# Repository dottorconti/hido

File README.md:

# HIDO - Arcade Multi-Mode Controller

Open source arcade controller with STM32F102RB microcontroller.

## 🎮 Features

- **Triple Mode Support**: NKRO Keyboard, Dual Joystick, or JVS/RS485
- **Ultra-Low Latency**: 1ms USB polling (1000Hz)
- **Plug & Play**: Standard USB HID device, no drivers needed
- **Hardware Debouncing**: 5ms configurable debounce time
- **Dual Player Support**: 2 independent joystick interfaces (34 inputs total)

## 📚 Documentation

### Quick Links
- **[📋 PINOUT.md](doc/PINOUT.md)** - Complete pin mapping and silkscreen reference
- **[🔧 Firmware Documentation](doc/README.md)** - Detailed firmware guide
- **[🔨 Build & Compilation](doc/COMPILATION.md)** - How to build the firmware (scripts and legacy method)
- **[⚡ Quick Start Guide](doc/QUICK_START.md)** - Get started quickly
- **[🔄 Mode Comparison](doc/MODE_COMPARISON.md)** - Keyboard vs Joystick vs JVS
- **[⚙️ Hardware Configuration](doc/HARDWARE_CONFIG.md)** - Hardware setup
- **[🕹️ JVS Protocol](doc/JVS_PROTOCOL.md)** - JVS/RS485 arcade protocol
- **[📝 Changelog](doc/CHANGELOG.md)** - Version history
- **[👥 Credits](doc/CREDITS.md)** - Contributors and licenses

## 🚀 Quick Start

1. **Connect your arcade controls** - See [PINOUT.md](doc/PINOUT.md) for connector pinout
2. **Select operating mode** - Edit `firmware/Core/Inc/usbd_hid_custom.h`
3. **Compile and flash** - See [Quick Start Guide](doc/QUICK_START.md)
4. **Plug and play** - Device recognized as USB HID

## 🛠️ Hardware

- **MCU**: STM32F102RB (Cortex-M3, 128KB Flash)
- **USB**: Full-Speed USB 2.0 (12 Mbps)
- **Connectors**: J6 (Player 1), J7 (Player 2) - 18 pins each
- **Inputs**: 34 digital inputs (17 per player) with pull-up resistors
- **LEDs**: Debug indicators (LED1=P1, LED2=P2)

## 📋 Pin Mapping Reference

Each connector has **silkscreen labels** (0-9, A-F, 10) for easy identification:

| Silkscreen | Pin | Player 1 Key | Player 2 Key |
|------------|-----|--------------|--------------|
| COM | 1 | GND | GND |
| 0 | 2 | Z | A |
| 1 | 3 | X | S |
| 2 | 4 | C | D |
| ... | ... | ... | ... |
| 10 | 18 | ↑ | F1 |

**See [PINOUT.md](doc/PINOUT.md) for complete mapping.**

## 🔌 Operating Modes

### Keyboard Mode (6KRO)
Standard USB keyboard with 6-key rollover for arcade gaming.

### Joystick Mode
Dual USB joystick with 13 logical buttons + 2 axes each (per player).

Note (recent fixes):
- Firmware expects 13 logical buttons per player (bits 0..12).
- Natural mapping restored: Report ID 1 -> Player 1, Report ID 2 -> Player 2.
- Removed blocking `HAL_Delay(1)` between HID reports to avoid USB freezes.
- Firmware now only sends HID reports when the report contents change (reduces USB traffic).
- If Player 2 feels slow, try reducing `DEBOUNCE_TIME_MS` in `Core/Inc/arcade_joystick.h` to 2-3 ms.

### JVS Mode
RS485 arcade I/O board protocol for JAMMA/JVS cabinets.

**See [Mode Comparison](doc/MODE_COMPARISON.md) for details.**

## 📦 Repository Structure

```
hido/
├── README.md
├── doc/                   # Documentation
│   ├── CHANGELOG.md
│   ├── CORREZIONI_RS485_5V.md
│   ├── CREDITS.md
│   ├── DFU_UPDATE.md
│   ├── HARDWARE_CONFIG.md
│   ├── JVS_PROTOCOL.md
│   ├── MODE_COMPARISON.md
│   ├── PINOUT.md
│   ├── QUICK_START.md
│   └── README.md
├── fabrication/           # Gerber / manufacturing files
├── firmware/              # STM32 firmware source and tools
│   ├── build.ps1
│   ├── check_dfu_util.bat
│   ├── compile_direct.ps1
│   ├── config_tool.py
│   ├── dfu_update.bat
│   ├── dfu_update.py
│   ├── download_dfu_util.bat
│   ├── flash.ps1
│   ├── hido.ioc
│   ├── LICENSE
│   ├── Makefile
│   ├── STM32F102RBTX_FLASH.ld
│   ├── Core/
│   │   ├── Inc/
│   │   ├── Src/
│   │   └── Startup/
│   ├── Drivers/
│   │   └── STM32F1xx_HAL_Driver/
│   ├── Middlewares/
│   │   └── ST/STM32_USB_Device_Library/
│   ├── tools/
│   └── USB_DEVICE/
├── hardware/              # KiCad design & PCB files
│   ├── Jopen.kicad_pcb
│   ├── Jopen.kicad_sch
│   ├── mcu.kicad_sch
│   ├── rs485.kicad_sch
│   └── Jopen-backups/     # local backups (should be ignored)
└── tools/                 # helper scripts and utilities
```

## 📄 License

See [CREDITS.md](doc/CREDITS.md) for license information.

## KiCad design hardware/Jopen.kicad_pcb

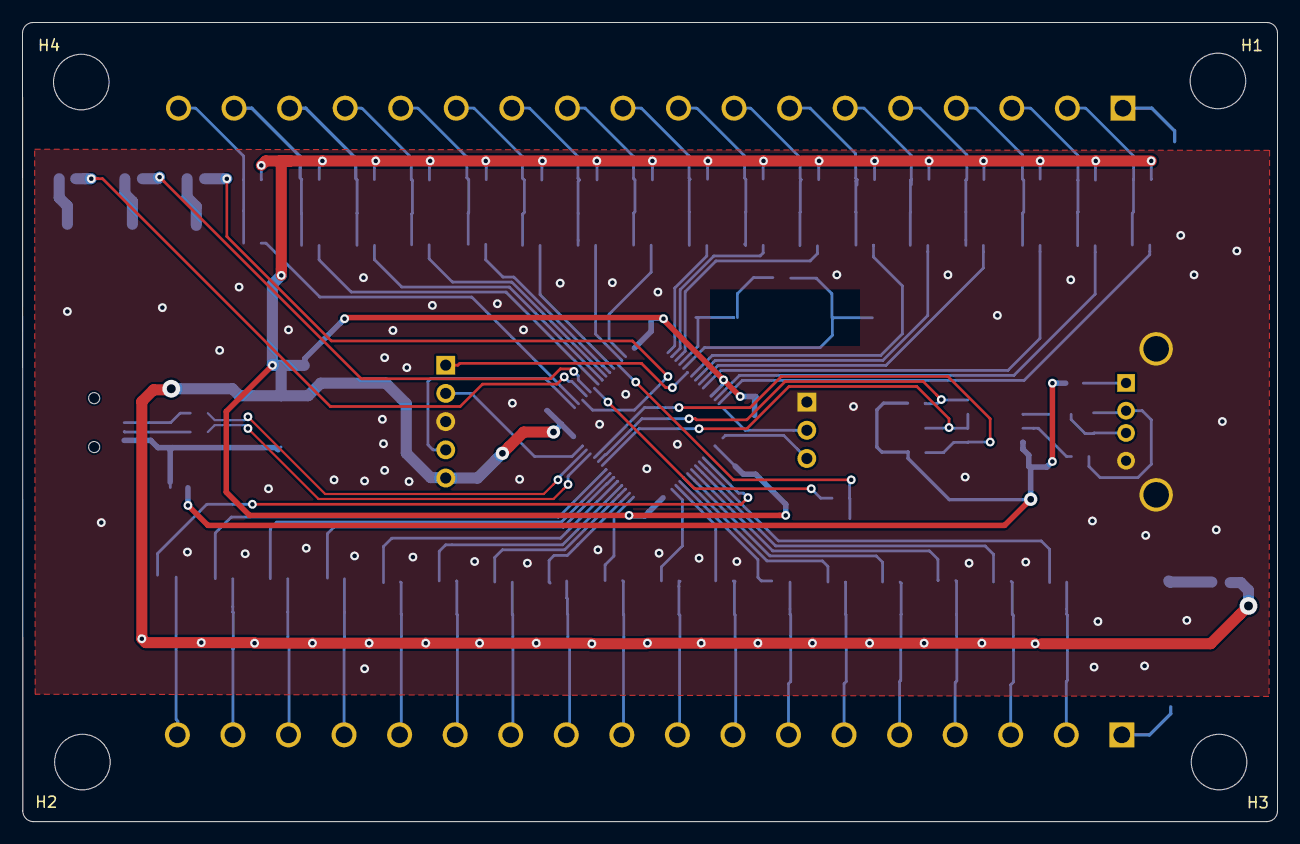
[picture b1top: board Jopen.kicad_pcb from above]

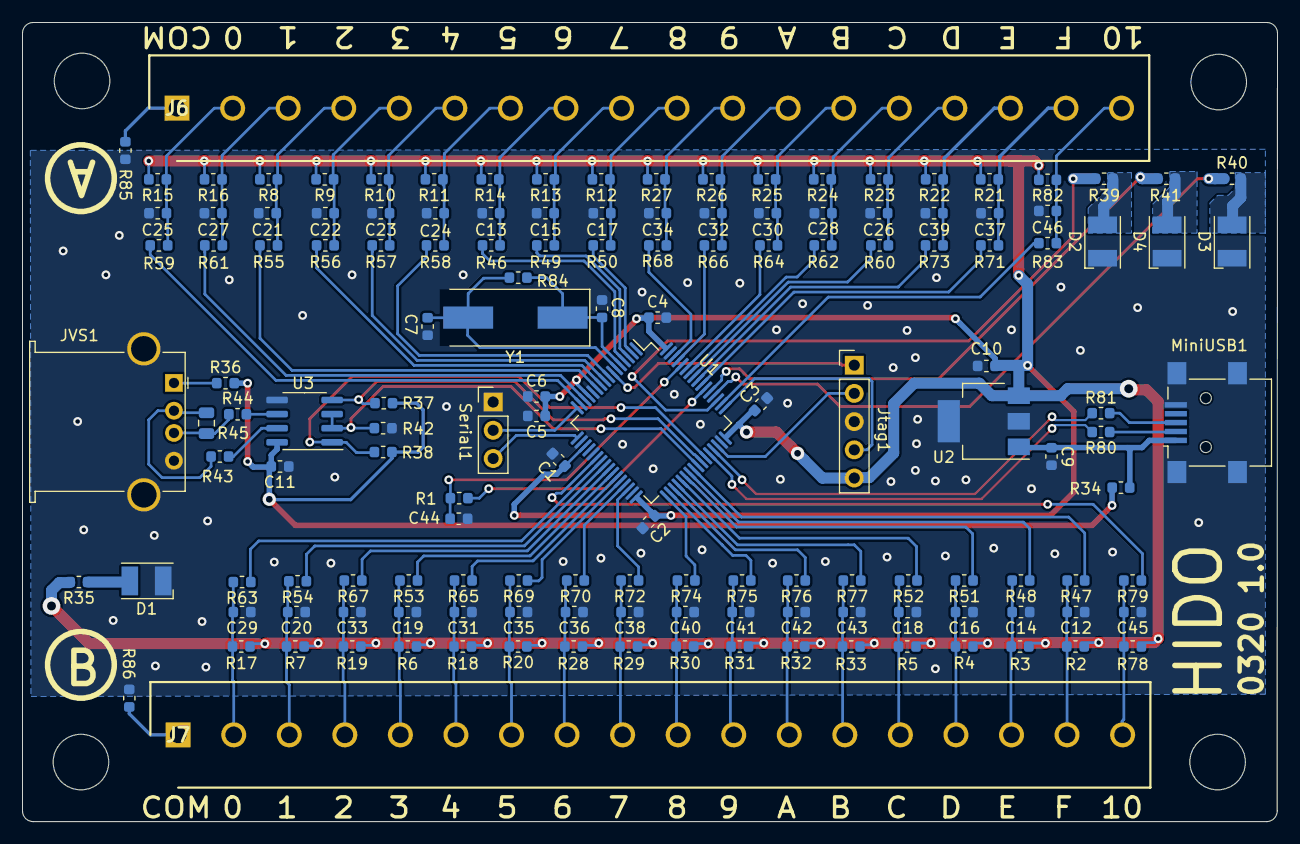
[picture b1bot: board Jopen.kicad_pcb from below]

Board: 2 copper layers, 113.0 x 71.9 mm, 150 parts (146 on the bottom side), 102 nets.

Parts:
C1, C2, C3, C4, C11: 100nF; C_0603_1608Metric
C5: 10nF; C_0603_1608Metric
C6, C44: 1uF; C_0603_1608Metric
C7, C8: 30pF; C_0603_1608Metric
C9: 10uF; C_0603_1608Metric
C10: 4,7uF; C_0603_1608Metric
C12, C13, C14, C15, C16, C17, C18, C19, C20, C21, C22, C23, C24, C25, C26, C27, C28, C29, C30, C31, C32, C33, C34, C35, C36, C37, C38, C39, C40, C41, C42, C43, C45, C46: 10pF; C_0603_1608Metric
D1, D2, D3, D4: LED; LED_PLCC-2
H1, H2, H3, H4: MountingHole; MountingHole_5mm
J6, J7: Screw_Terminal_01x18; SHDR18W130P0X500_1X18_9000X950X1500P
JVS1: JVS; USB_A_Stewart_SS-52100-001_Horizontal
Jtag1: Conn_01x05; PinHeader_1x05_P2.54mm_Vertical
MiniUSB1: USB_B_Mini; USB_Mini-B_Lumberg_2486_01_Horizontal
R1, R2, R3, R4, R5, R6, R7, R8, R9, R10, R11, R12, R13, R14, R15, R16, R17, R18, R19, R20, R21, R22, R23, R24, R25, R26, R27, R28, R29, R30, R31, R32, R33, R37, R38, R42, R78, R82: 10k; R_0603_1608Metric
R34, R36, R43, R44, R80, R81, R85, R86: 0R; R_0603_1608Metric
R35, R39, R40, R41: 150R; R_0603_1608Metric
R45: 120R; R_0805_2012Metric
R46, R47, R48, R49, R50, R51, R52, R53, R54, R55, R56, R57, R58, R59, R60, R61, R62, R63, R64, R65, R66, R67, R68, R69, R70, R71, R72, R73, R74, R75, R76, R77, R79, R83: 100R; R_0603_1608Metric
R84: 1M; R_0603_1608Metric
Serial1: Conn_01x03; PinHeader_1x03_P2.54mm_Vertical
U1: STM32F102RBTx; LQFP-64_10x10mm_P0.5mm
U2: TPS7B6933QDCYRQ1; SOT-223-3_TabPin2
U3: SN65HVD1786D; SOIC-8_3.9x4.9mm_P1.27mm
Y1: 8 MHz; Crystal_SMD_HC49-SD

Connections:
+3V3: C1.1, C2.1, C3.1, C4.1, C5.1, C6.1, C10.1, Jtag1.5, R2.2, R3.2, R4.2, R5.2, R6.2, R7.2, R8.2, R9.2, R10.2, R11.2, R12.2, R13.2, R14.2, R15.2, R16.2, R17.2, R18.2, R19.2, R20.2, R21.2, R22.2, R23.2, R24.2, R25.2, R26.2, R27.2, R28.2, R29.2, R30.2, R31.2, R32.2, R33.2, R35.2, R78.2, R82.2, U1.13, U1.19, U1.32, U1.48, U1.64, U2.3
+5V: C11.1, R34.2, R36.2, R37.2, R38.2, U3.8
/NRST: Jtag1.1, U1.7
/SYS_SWCLK: Jtag1.4, U1.49
/SYS_SWDIO: Jtag1.2, U1.46
/USB_D_N: R80.2, U1.44
/USB_D_P: R81.2, U1.45
/mcu/ADC1: C21.2, J6.4, R8.1, R55.2
/mcu/ADC2: C22.2, J6.5, R9.1, R56.2
/mcu/ADC3: C19.2, J7.5, R6.1, R53.2
/mcu/ADC4: C31.2, J7.6, R18.1, R65.2
/mcu/IN1: C23.2, J6.6, R10.1, R57.2
/mcu/IN2: C24.2, J6.7, R11.1, R58.2
/mcu/IN3: C13.2, J6.8, R14.1, R46.2
/mcu/IN4: C15.2, J6.9, R13.1, R49.2
/mcu/IN5: C17.2, J6.10, R12.1, R50.2
/mcu/IN6: C34.2, J6.11, R27.1, R68.2
/mcu/IN7: C32.2, J6.12, R26.1, R66.2
/mcu/IN8: C30.2, J6.13, R25.1, R64.2
/mcu/IN9: C28.2, J6.14, R24.1, R62.2
/mcu/IN10: C26.2, J6.15, R23.1, R60.2
/mcu/IN11: C39.2, J6.16, R22.1, R73.2
/mcu/IN12: C37.2, J6.17, R21.1, R71.2
/mcu/IN13: C29.2, J7.2, R17.1, R63.2
/mcu/IN14: C20.2, J7.3, R7.1, R54.2
/mcu/IN15: C33.2, J7.4, R19.1, R67.2
/mcu/IN16: C35.2, J7.7, R20.1, R69.2
/mcu/IN17: C36.2, J7.8, R28.1, R70.2
/mcu/IN18: C38.2, J7.9, R29.1, R72.2
/mcu/IN19: C40.2, J7.10, R30.1, R74.2
/mcu/IN20: C41.2, J7.11, R31.1, R75.2
/mcu/IN21: C42.2, J7.12, R32.1, R76.2
/mcu/IN22: C43.2, J7.13, R33.1, R77.2
/mcu/IN23: C14.2, J7.16, R3.1, R48.2
/mcu/IN24: C12.2, J7.17, R2.1, R47.2
/mcu/IN25: C45.2, J7.18, R78.1, R79.2
/mcu/IN26: C46.2, J6.18, R82.1, R83.2
/mcu/LED1: R39.1, U1.51
/mcu/LED2: R40.1, U1.52
/mcu/LED3: R41.1, U1.53
/mcu/OSC_IN: C8.1, R84.1, U1.5, Y1.1
/mcu/OSC_OUT: C7.1, R84.2, U1.6, Y1.2
/mcu/TIM1: C25.2, J6.2, R15.1, R59.2
/mcu/TIM2: C27.2, J6.3, R16.1, R61.2
/mcu/TIM3: C18.2, J7.14, R5.1, R52.2
/mcu/TIM4: C16.2, J7.15, R4.1, R51.2
/mcu/USART_EN_JVC: R42.2, U1.41, U3.2, U3.3
/mcu/USART_RX: Serial1.3, U1.17
/mcu/USART_RX_JVC: R38.1, U1.43, U3.1
/mcu/USART_TX: Serial1.2, U1.16
/mcu/USART_TX_JVC: R37.1, U1.42, U3.4
/mcu/uC_ADC1: R55.1, U1.11
/mcu/uC_ADC2: R56.1, U1.10
/mcu/uC_ADC3: R53.1, U1.26
/mcu/uC_ADC4: R65.1, U1.27
/mcu/uC_IN1: R57.1, U1.9
/mcu/uC_IN2: R58.1, U1.8
/mcu/uC_IN3: R46.1, U1.4
/mcu/uC_IN4: R49.1, U1.3
/mcu/uC_IN5: R50.1, U1.2
/mcu/uC_IN6: R68.1, U1.62
/mcu/uC_IN7: R66.1, U1.61
/mcu/uC_IN8: R64.1, U1.59
/mcu/uC_IN9: R62.1, U1.58
/mcu/uC_IN10: R60.1, U1.57
/mcu/uC_IN11: R73.1, U1.56
/mcu/uC_IN12: R71.1, U1.55
/mcu/uC_IN13: R63.1, U1.23
/mcu/uC_IN14: R54.1, U1.24
/mcu/uC_IN15: R67.1, U1.25
/mcu/uC_IN16: R69.1, U1.28
/mcu/uC_IN17: R70.1, U1.29
/mcu/uC_IN18: R72.1, U1.30
/mcu/uC_IN19: R74.1, U1.33
/mcu/uC_IN20: R75.1, U1.34
/mcu/uC_IN21: R76.1, U1.35
/mcu/uC_IN22: R77.1, U1.36
/mcu/uC_IN23: R48.1, U1.39
/mcu/uC_IN24: R47.1, U1.40
/mcu/uC_IN25: R79.1, U1.22
/mcu/uC_IN26: R83.1, U1.50
/mcu/uC_TIM1: R59.1, U1.15
/mcu/uC_TIM2: R61.1, U1.14
/mcu/uC_TIM3: R52.1, U1.37
/mcu/uC_TIM4: R51.1, U1.38
/rs485/rs485_A: JVS1.3, R44.1, R45.1
/rs485/rs485_B: JVS1.2, R43.1, R45.2
GND: C1.2, C2.2, C3.2, C4.2, C5.2, C6.2, C7.2, C8.2, C9.2, C10.2, C11.2, C12.1, C13.1, C14.1, C15.1, C16.1, C17.1, C18.1, C19.1, C20.1, C21.1, C22.1, C23.1, C24.1, C25.1, C26.1, C27.1, C28.1, C29.1, C30.1, C31.1, C32.1, C33.1, C34.1, C35.1, C36.1, C37.1, C38.1, C39.1, C40.1, C41.1, C42.1, C43.1, C44.2, C45.1, C46.1, D1.1, D2.1, D3.1, D4.1, JVS1.4, JVS1.5, Jtag1.3, MiniUSB1.5, MiniUSB1.6, R42.1, R85.1, R86.2, Serial1.1, U1.12, U1.18, U1.31, U1.47, U1.63, U2.2, U3.5
unnamed: C9.1, MiniUSB1.1, R34.1, U2.1
unnamed: C44.1, R1.1, U1.60
unnamed: D1.2, R35.1
unnamed: D2.2, R39.2
unnamed: D3.2, R40.2
unnamed: D4.2, R41.2
unnamed: J6.1, R85.2
unnamed: J7.1, R86.1
unnamed: JVS1.1, R36.1
unnamed: MiniUSB1.2, R80.1
unnamed: MiniUSB1.3, R81.1
unnamed: R1.2, U1.54
unnamed: R43.2, U3.7
unnamed: R44.2, U3.6

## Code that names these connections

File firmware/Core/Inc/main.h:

/* USER CODE BEGIN Header */
/**
  ******************************************************************************
  * @file           : main.h
  * @brief          : Header for main.c file.
  *                   This file contains the common defines of the application.
  ******************************************************************************
  * @attention
  *
  * <h2><center>&copy; Copyright (c) 2020 STMicroelectronics.
  * All rights reserved.</center></h2>
  *
  * This software component is licensed by ST under BSD 3-Clause license,
  * the "License"; You may not use this file except in compliance with the
  * License. You may obtain a copy of the License at:
  *                        opensource.org/licenses/BSD-3-Clause
  *
  ******************************************************************************
  */
/* USER CODE END Header */

/* Define to prevent recursive inclusion -------------------------------------*/
#ifndef __MAIN_H
#define __MAIN_H

#ifdef __cplusplus
extern "C" {
#endif

/* Includes ------------------------------------------------------------------*/
#include "stm32f1xx_hal.h"

/* Private includes ----------------------------------------------------------*/
/* USER CODE BEGIN Includes */

/* USER CODE END Includes */

/* Exported types ------------------------------------------------------------*/
/* USER CODE BEGIN ET */

/* USER CODE END ET */

/* Exported constants --------------------------------------------------------*/
/* USER CODE BEGIN EC */

/* USER CODE END EC */

/* Exported macro ------------------------------------------------------------*/
/* USER CODE BEGIN EM */

/* USER CODE END EM */

/* Exported functions prototypes ---------------------------------------------*/
void Error_Handler(void);

/* Enable continuous composite blink (set by composite Init) */
extern volatile uint8_t composite_blink_enabled;

/* USER CODE BEGIN EFP */

/* USER CODE END EFP */

/* Private defines -----------------------------------------------------------*/
#define LED1_Pin GPIO_PIN_10
#define LED1_GPIO_Port GPIOC
#define LED2_Pin GPIO_PIN_11
#define LED2_GPIO_Port GPIOC
#define LED3_Pin GPIO_PIN_12
#define LED3_GPIO_Port GPIOC

/* USER CODE BEGIN Private defines */

/* Player 1 Controls (J6 Connector) - 4 Axes + 13 Buttons */
// Joystick directional inputs - mapped to IN26, IN12, IN11, IN10
#define P1_UP_Pin GPIO_PIN_15       // J6 Pin 18 - IN26
#define P1_UP_GPIO_Port GPIOA
#define P1_DOWN_Pin GPIO_PIN_3      // J6 Pin 17 - IN12
#define P1_DOWN_GPIO_Port GPIOB
#define P1_LEFT_Pin GPIO_PIN_4      // J6 Pin 16 - IN11
#define P1_LEFT_GPIO_Port GPIOB
#define P1_RIGHT_Pin GPIO_PIN_5     // J6 Pin 15 - IN10
#define P1_RIGHT_GPIO_Port GPIOB

// Player 1 buttons (13 buttons) - use TIM1, TIM2, ADC1, ADC2 and remaining inputs
#define P1_BTN1_Pin GPIO_PIN_1      // J6 Pin 2 - TIM1
#define P1_BTN1_GPIO_Port GPIOA
#define P1_BTN2_Pin GPIO_PIN_0      // J6 Pin 3 - TIM2
#define P1_BTN2_GPIO_Port GPIOA
#define P1_BTN3_Pin GPIO_PIN_2      // J6 Pin 4 - ADC1
#define P1_BTN3_GPIO_Port GPIOC
#define P1_BTN4_Pin GPIO_PIN_3      // J6 Pin 5 - ADC2
#define P1_BTN4_GPIO_Port GPIOC
#define P1_BTN5_Pin GPIO_PIN_1      // J6 Pin 6 - IN1
#define P1_BTN5_GPIO_Port GPIOC
#define P1_BTN6_Pin GPIO_PIN_0      // J6 Pin 7 - IN2
#define P1_BTN6_GPIO_Port GPIOC
#define P1_BTN7_Pin GPIO_PIN_15     // J6 Pin 8 - IN3
#define P1_BTN7_GPIO_Port GPIOC
#define P1_BTN8_Pin GPIO_PIN_14     // J6 Pin 9 - IN4
#define P1_BTN8_GPIO_Port GPIOC
#define P1_BTN9_Pin GPIO_PIN_13     // J6 Pin 10 - IN5
#define P1_BTN9_GPIO_Port GPIOC
#define P1_BTN10_Pin GPIO_PIN_9     // J6 Pin 11 - IN6
#define P1_BTN10_GPIO_Port GPIOB
#define P1_BTN11_Pin GPIO_PIN_8     // J6 Pin 12 - IN7
#define P1_BTN11_GPIO_Port GPIOB
#define P1_BTN12_Pin GPIO_PIN_7     // J6 Pin 13 - IN8
#define P1_BTN12_GPIO_Port GPIOB
#define P1_BTN13_Pin GPIO_PIN_6     // J6 Pin 14 - IN9
#define P1_BTN13_GPIO_Port GPIOB

/* Player 2 Controls (J7 Connector) - 4 Axes + 13 Buttons */
// Joystick directional inputs - keep same as before
#define P2_UP_Pin GPIO_PIN_6        // J7 Pin 18 - IN25
#define P2_UP_GPIO_Port GPIOA
#define P2_DOWN_Pin GPIO_PIN_9      // J7 Pin 17 - IN24
#define P2_DOWN_GPIO_Port GPIOC
#define P2_LEFT_Pin GPIO_PIN_8      // J7 Pin 16 - IN23
#define P2_LEFT_GPIO_Port GPIOC
#define P2_RIGHT_Pin GPIO_PIN_7     // J7 Pin 15 - TIM4
#define P2_RIGHT_GPIO_Port GPIOC

// Player 2 buttons (13 buttons) - skip ADC3/4 (PB0/PB1)
#define P2_BTN1_Pin GPIO_PIN_7      // J7 Pin 2 - IN13
#define P2_BTN1_GPIO_Port GPIOA
#define P2_BTN2_Pin GPIO_PIN_4      // J7 Pin 3 - IN14
#define P2_BTN2_GPIO_Port GPIOC
#define P2_BTN3_Pin GPIO_PIN_5      // J7 Pin 4 - IN15
#define P2_BTN3_GPIO_Port GPIOC
#define P2_BTN4_Pin GPIO_PIN_2      // J7 Pin 7 - IN16
#define P2_BTN4_GPIO_Port GPIOB
#define P2_BTN5_Pin GPIO_PIN_10     // J7 Pin 8 - IN17
#define P2_BTN5_GPIO_Port GPIOB
#define P2_BTN6_Pin GPIO_PIN_11     // J7 Pin 9 - IN18
#define P2_BTN6_GPIO_Port GPIOB
#define P2_BTN7_Pin GPIO_PIN_12     // J7 Pin 10 - IN19
#define P2_BTN7_GPIO_Port GPIOB
#define P2_BTN8_Pin GPIO_PIN_13     // J7 Pin 11 - IN20
#define P2_BTN8_GPIO_Port GPIOB
#define P2_BTN9_Pin GPIO_PIN_14     // J7 Pin 12 - IN21
#define P2_BTN9_GPIO_Port GPIOB
#define P2_BTN10_Pin GPIO_PIN_15    // J7 Pin 13 - IN22
#define P2_BTN10_GPIO_Port GPIOB
#define P2_BTN11_Pin GPIO_PIN_6     // J7 Pin 14 - TIM3
#define P2_BTN11_GPIO_Port GPIOC
#define P2_BTN12_Pin GPIO_PIN_0     // J7 Pin 5 - ADC3 (as button, for compatibility)
#define P2_BTN12_GPIO_Port GPIOB
#define P2_BTN13_Pin GPIO_PIN_1     // J7 Pin 6 - ADC4 (as button, for compatibility)
#define P2_BTN13_GPIO_Port GPIOB

/* USER CODE END Private defines */

#ifdef __cplusplus
}
#endif

#endif /* __MAIN_H */

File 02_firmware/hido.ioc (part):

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Mcu.Name=STM32F102R(8-B)Tx
Mcu.Package=LQFP64
Mcu.UserName=STM32F102RBTx
PA0-WKUP.Signal=S_TIM2_CH1_ETR
PA1.Signal=S_TIM2_CH2
PA10.Mode=Asynchronous
PA10.Signal=USART1_RX
PA11.Mode=Device
PA11.Signal=USB_DM
PA12.Mode=Device
PA12.Signal=USB_DP
PA13.Mode=Serial_Wire
PA13.Signal=SYS_JTMS-SWDIO
PA14.Mode=Serial_Wire
PA14.Signal=SYS_JTCK-SWCLK
PA15.Signal=GPIO_Input
PA2.Mode=Asynchronous
PA2.Signal=USART2_TX
PA3.Mode=Asynchronous
PA3.Signal=USART2_RX
PA6.Signal=GPIO_Input
PA7.Signal=GPIO_Input
PA8.Signal=GPIO_Output
PA9.Mode=Asynchronous
PA9.Signal=USART1_TX
PB0.Signal=ADCx_IN8
PB1.Signal=ADCx_IN9
PB10.Signal=GPIO_Input
PB11.Signal=GPIO_Input
PB12.Signal=GPIO_Input
PB13.Signal=GPIO_Input
PB14.Signal=GPIO_Input
PB15.Signal=GPIO_Input
PB2.Signal=GPIO_Input
PB3.Signal=GPIO_Input
PB4.Signal=GPIO_Input
PB5.Signal=GPIO_Input
PB6.Signal=GPIO_Input
PB7.Signal=GPIO_Input
PB8.Signal=GPIO_Input
PB9.Signal=GPIO_Input
PC0.Signal=GPIO_Input
PC1.Signal=GPIO_Input
PC10.GPIOParameters=GPIO_Label
PC10.GPIO_Label=LED1
PC10.Signal=GPIO_Output
PC11.GPIOParameters=GPIO_Label
PC11.GPIO_Label=LED2
PC11.Signal=GPIO_Output
PC12.GPIOParameters=GPIO_Label
PC12.GPIO_Label=LED3
PC12.Signal=GPIO_Output
PC13-TAMPER-RTC.Signal=GPIO_Input
PC14-OSC32_IN.Signal=GPIO_Input
PC15-OSC32_OUT.Signal=GPIO_Input
PC2.Signal=ADCx_IN12
PC3.Signal=ADCx_IN13
PC4.Signal=GPIO_Output
PC5.Signal=GPIO_Input
PC6.Signal=GPIO_Input
PC7.Signal=GPIO_Input
PC8.Signal=GPIO_Input
PC9.Signal=GPIO_Input
PD0-OSC_IN.Mode=HSE-External-Oscillator
PD0-OSC_IN.Signal=RCC_OSC_IN
PD1-OSC_OUT.Mode=HSE-External-Oscillator
PD1-OSC_OUT.Signal=RCC_OSC_OUT
PD2.Signal=GPIO_Output
RCC.SYSCLKFreq_VALUE=48000000
RCC.SYSCLKSource=RCC_SYSCLKSOURCE_PLLCLK
board=custom

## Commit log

2020-05-05 STM32 device detected
2020-05-07 added schematic pdf and pcb image
2025-11-10 Complete firmware rewrite with NKRO keyboard and JVS protocol support
    Major improvements after 5 years:
    - Replaced obsolete 2015 USB libraries with modern STM32 HAL drivers
    - Implemented NKRO (N-Key Rollover) supporting up to 96 simultaneous keys
    - Reduced USB polling from 10ms to 1ms (1000Hz) for ultra-low latency
    - Added proper GPIO pull-ups for arcade buttons (normally-open, active LOW)
    - Implemented 5ms software debouncing
2025-11-10 Add credits and references to OpenJVS project
    - Added CREDITS.md with full attribution to OpenJVS (GPL-3.0)
    - Added LICENSE file (MIT) with third-party notices
    - Updated jvs_protocol.c/h headers with OpenJVS reference
    - Updated README.md with acknowledgments section
    - Updated JVS_PROTOCOL.md with OpenJVS credits
    Acknowledges:
2025-11-10 Add Dual Joystick mode - Triple mode support
    NEW FEATURE: Dual Joystick Mode
    - Emulates 2 independent USB HID joysticks (Player 1 & 2)
    - 16 buttons + 2 axes (X, Y) per joystick
    - Same hardware, switchable via compile-time define
    - Perfect for modern PC games and fighting games
    MODES NOW SUPPORTED:
2025-11-10 Fix joystick mode - USB HID descriptor corrections
    FIXES:
    - Removed Report ID from joystick descriptor (single joystick mode)
    - Changed interface protocol from 0x02 (mouse) to 0x00 (joystick)
    - Changed interface subclass from 0x01 (boot) to 0x00 (no boot)
    - Fixed joystick report size: 5 bytes -> 4 bytes (no ID field)
    - Corrected HID descriptor size: 54 -> 50 bytes
2025-11-10 Fix USB device strings for proper Windows recognition
    CRITICAL FIX:
    - Changed USB product string from 'STM32 Human interface' to mode-specific names
    - This fixes Windows driver errors and device recognition issues
    NEW DEVICE STRINGS:
    - Joystick Mode: 'HIDO Arcade Joystick'
    - Keyboard Mode: 'HIDO Arcade Keyboard'
2025-11-10 Implement dual joystick support with Report ID
    MAJOR UPDATE: Two separate joysticks instead of single joystick
    Changes:
    - HID descriptor: Added Report ID support for 2 joysticks
    - Descriptor size: 50 -> 78 bytes (two Application collections)
    - Report structure: Added report_id field (5 bytes: ID + X + Y + 16 buttons)
    - Report ID 1: Player 1 joystick
2025-11-10 Fix critical HID descriptor issues
    CRITICAL FIXES for Windows recognition:
    1. Report descriptor size: Fixed wItemLength field
    - Changed from single byte to proper 16-bit value
    - Now uses LOBYTE/HIBYTE macros correctly
    - Size 78 (0x4E) now properly encoded as [0x4E, 0x00]
    2. Interface protocol: Fixed remaining descriptor
2025-11-10 Fix HID report descriptor syntax error
    CRITICAL FIX for 'Unknown element in report descriptor' error:
    Problem: LOGICAL_MINIMUM was incorrectly encoded
    - Old: 0x15, 0x81 (invalid - 0x15 is for unsigned 1-byte values)
    - New: 0x16, 0x00, 0x80 (correct - 0x16 is for signed 2-byte values)
    Changes:
    - Changed LOGICAL_MINIMUM from 0x15 (1 byte) to 0x16 (2 bytes)
2025-11-10 Working single joystick implementation
    SUCCESS: Device now recognized as game controller in Windows!
    Root cause of previous errors:
    1. Hardcoded descriptor size in GET_DESCRIPTOR (was 50, needed 42)
    2. Incorrect byte count in descriptor array declaration
    Current implementation:
    - Single joystick (Player 1 only for now)
2025-11-10 Fix USB HID joystick enumeration - 3 critical bugs corrected
    - Fix #1: HID descriptor size mismatch (was 42 bytes defined, actual 39 bytes)
    Updated to correct 43 bytes with proper structure
    - Fix #2: Added missing USAGE(Pointer) and COLLECTION(Physical) for axes
    HID 1.11 specification requires Physical collection for analog inputs
    - Fix #3: Changed LOGICAL_MAXIMUM encoding from short (0x25,0xFF) to long form (0x26,0xFF,0x00)
    Proper encoding for values >127
2025-11-10 Implement dual arcade joystick with 14 buttons each
    Features implemented:
    - Expanded from 8 to 14 buttons per joystick (Player 1 and Player 2)
    - Added Report ID support for dual joystick configuration
    * Player 1: Report ID 1
    * Player 2: Report ID 2
    - HID Report: 5 bytes (1 Report ID + 2 axes + 2 bytes buttons with padding)
2025-11-10 Add custom HID descriptor files (best practice approach)
    Problem addressed:
    - Previous commits (b76fa87, c5c3dc6) modified middleware files directly
    - STM32CubeMX regeneration would overwrite these changes
    - Not following STMicroelectronics best practices
    Solution implemented:
    - Created Core/Inc/usbd_hid_custom.h with custom HID config
2025-11-10 Fix: Dual joystick with TWO Application Collections (2 separate devices, 14 buttons + 2 axes each) - descriptor size corrected to 102 bytes
2025-11-11 Docs: Update all documentation for dual joystick mode (14 buttons, TWO Application Collections, 102 bytes descriptor)
2025-11-11 Cleanup: Remove obsolete files ([ATT]5054.c, [ATT]5055.h, ISTRUZIONI_UTENTE.md) and update HARDWARE_CONFIG.md for joystick mode
2025-11-11 Fix GPIO configuration: PA0/PA1 non configurati e PC4 come OUTPUT
    - Aggiunto PA0, PA1 come GPIO_INPUT con GPIO_NOPULL per P1_UP/P1_DOWN
    - Corretto PC4 da OUTPUT a INPUT per P2_BTN2
    - Aggiunto tool diagnostico GPIO per test via UART
    - Aggiunto script compile_direct.ps1 per compilazione senza Make
    - Documentazione completa delle correzioni
2025-11-12 Fix P1 IN3 and P2 ADC4 pin configuration
    Firmware changes:
    - Disabled ADC peripheral initialization (MX_ADC1_Init and HAL_ADC_MspInit)
    - Added GPIO pull-up resistors for all button inputs (active-low logic)
    - Fixed keyboard HID descriptor (6KRO standard format, 47 bytes)
    - Added LED debug indicators (LED1=P1, LED2=P2)
    - Device name now conditional based on mode (Keyboard/Joystick/JVS)
2025-11-12 Fix GPIO configuration for PB1 and PC15 - all buttons working
    - Fixed PB1 (ADC4/P2_BTN13): removed from ADC configuration, forced as GPIO input
    - Fixed PC15 (IN3/P1_BTN7): reset Backup Domain to release from OSC32, aggressive GPIO config
    - Increased MAX_BUTTONS from 32 to 40 in keyboard mode
    - Extended joystick mode support from 13 to 14 buttons
    - Updated flash.ps1 to auto-detect STM32CubeProgrammer path
    - Hardware issue on PC15 resolved (bad solder joint on resistor)
2025-11-12 Remove KiCad lock files and add them to .gitignore
2025-11-13 Add complete pinout mapping documentation
    - Added PINOUT.md with silkscreen to key mapping
    - Documented J6/J7 connector pinouts with COM (Pin 1)
    - Silkscreen labels: 0-9, A-F, 10 correspond to pins 2-18
    - Complete mapping for both Player 1 (J6) and Player 2 (J7)
    - Added technical details for developers and usage notes for end users
2025-11-13 Clean up obsolete debug and temporary documentation
    Removed 6 temporary/debug markdown files:
    - RIEPILOGO_FINALE.md (debug notes - issues resolved)
    - START_HERE.md (temporary debug guide)
    - CORREZIONI.md (corrections already in CHANGELOG)
    - PIN_MAPPING_CHECK.md (replaced by PINOUT.md)
    - GPIO_TEST_GUIDE.md (debug tool guide - no longer needed)
2025-11-13 Update documentation and remove KiCad lock files
    Documentation updates:
    - Updated README.md with comprehensive navigation links
    - Added cross-references between all documentation files
    - Improved project overview and structure
    - Added back navigation in PINOUT.md
    Cleanup:
2025-11-13 Add USB DFU bootloader with automatic entry via Python
    Firmware implementation:
    - dfu_bootloader.c/h: PD2 controls BOOT0 via 1kΩ + capacitor
    - usb_commands.c/h: USB vendor commands (0xBB = enter bootloader)
    - usbd_hid.c: Added USB_REQ_TYPE_VENDOR handler
    - Hardware: R=1kΩ, delay=10ms optimized for fast charge
    Python automation:
2025-11-13 Fix: Add DFU source files to build script and missing USB header
    - Added dfu_bootloader.c and usb_commands.c to compile_direct.ps1
    - Added usbd_core.h include for USBD_CtlSendData function
    - Firmware now compiles successfully with DFU support (16.4 KB)
2025-11-13 feat: Add USB configuration system with FLASH persistence
    - Implemented flash_config.c/h for EEPROM emulation (last 2KB page)
    - Added USB vendor commands: 0xC0 (read), 0xC1 (write), 0xC2 (reset)
    - CRC32 validation for config integrity
    - Support for both keyboard and joystick mode configurations
    - Auto-load config from FLASH on startup with fallback to defaults
    - Python config_tool.py for USB configuration management
2025-11-13 feat: Add tools folder with DFU and config utilities
    - dfu-util.exe (v0.11 static with embedded libusb)
    - dfu_update.py and dfu_update.bat for firmware update
    - config_tool.py for USB pin mapping configuration
    - libusb-1.0.dll for Windows pyusb support
    - Complete README.md with usage instructions and troubleshooting
2025-11-14 Firmware: add RAW HID interface stubs, fix descriptors, restore HID registration
2025-11-17 Joystick: restore natural mapping, remove HAL_Delay, send only changed reports; update firmware README
2025-11-17 Docs: document recent joystick fixes (mapping, debounce, USB timing)
2025-11-18 chore(docs): move firmware docs to doc/, sync HARDWARE_CONFIG.md with firmware macros; update build scripts
2025-11-18 docs: point README to doc/PINOUT.md
2025-11-18 docs: point PINOUT links to doc/firmware/PINOUT.md
2025-11-18 chore(docs): commit updated markdown files
2025-11-18 correct README.md
2025-11-18 chore(docs): flatten docs into doc/ and update links
2025-11-18 fix(joystick): enforce 13-buttons per player in mapping and masking
2025-11-18 Add hardware/Jopen-backups to .gitignore and remove tracked backups
2025-11-18 Rimuovi file cancellati
2025-11-18 Move pdf file in fabrication
2025-11-18 Docs: add STM32CubeIDE warning and detected library versions to COMPILATION.md
2025-11-18 HID: prefer project custom joystick descriptor when USE_JOYSTICK_MODE is enabled
2025-11-18 VirtualCOM: add minimal ST CDC class, composite class and CDC descriptors; register composite
2025-11-18 Composite: call CDC helpers; fix serial string descriptor header
2025-11-19 Add composite GetUsrStrDescriptor for per-interface HID strings
2025-11-19 wip: save local changes before virtualcom work
2025-11-19 feat(usb): reserve PMA regions for CDC endpoints (prepare composite)
2025-11-19 chore(usb): remove HID_RAW interface and exclude usbd_hid_raw from build (prepare CDC)
2025-11-19 feat(usb): composite HID+CDC skeleton, remove RAW HID, update descriptors and PMA
2025-11-20 virtualcom: add CDC ACM (virtual COM), CDC-only test, LED diagnostics
2025-11-20 hid: 30-button HID report descriptor (Report ID 0x03) compatible with Joystick library
2025-11-20 hid: add helper to send Arduino-compatible 30-button report (Report ID 0x03)
2025-11-20 hid: combined descriptor - keep 2 joysticks (ID1/ID2) and add Arduino-style 30-button device (ID3)
2025-12-01 Pulizia composite HID+CDC: rimosso HID RAW, debounce joystick migliorato, placeholder report JVS (1 byte), semplificato usbd_desc fallback, eliminati warning e duplicati.
2025-12-01 feat: implementazione USB Composite HID+CDC funzionante
    - Aggiunta classe USBD_COMPOSITE con routing HID e CDC
    - Fix HID_EPIN_SIZE da 6 a 64 byte per supporto dual joystick
    - Implementato wrapper USBD_COMPOSITE_HID_SendReport per pClassData switching
    - Fix DataIn routing: rimosso bit direzionale 0x80 dai controlli endpoint
    - Fix Get_SerialNum: rimossa ottimizzazione prematura che bloccava init buffer
    - CDC minimale con line coding 115200 8N1 e deferred PrepareReceive
